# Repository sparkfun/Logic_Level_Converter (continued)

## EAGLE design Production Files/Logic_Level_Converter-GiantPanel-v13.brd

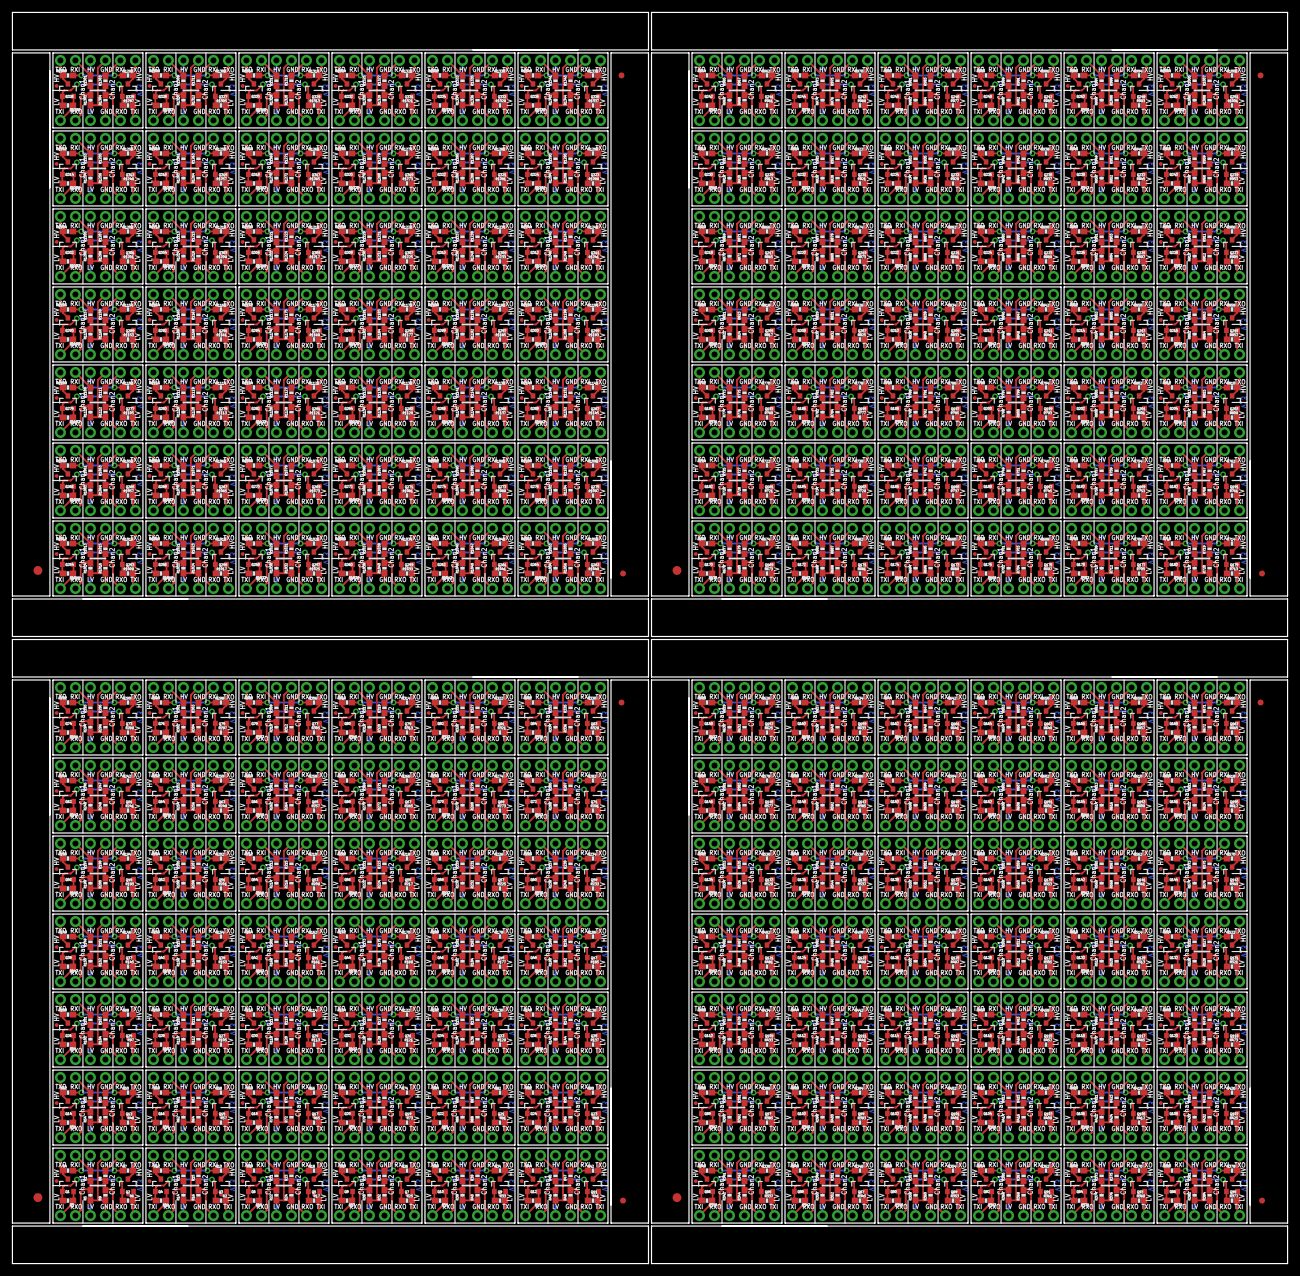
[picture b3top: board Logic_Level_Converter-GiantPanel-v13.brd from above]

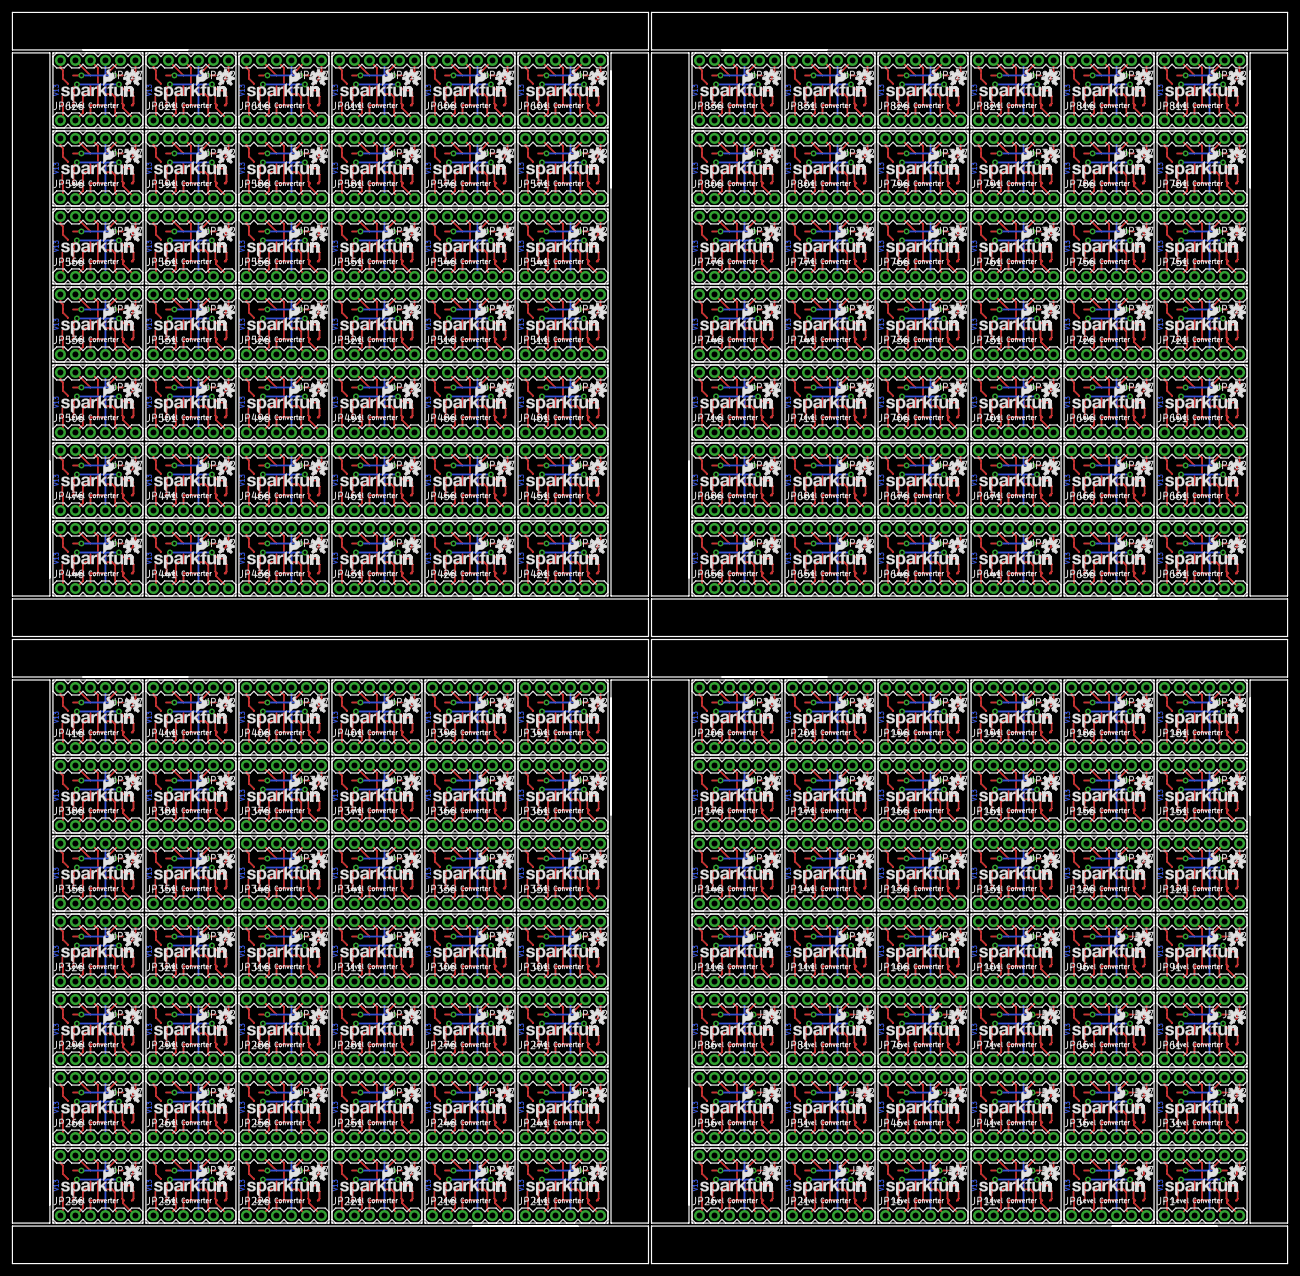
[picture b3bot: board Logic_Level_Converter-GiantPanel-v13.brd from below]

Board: 2 copper layers, 215.9 x 211.8 mm, 2868 parts (840 on the bottom side), 1848 nets.

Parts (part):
E$1, E$6, E$9, E$12: FIDUCIAL-1.5X3
E$2, E$3, E$4, E$5, E$7, E$8, E$10, E$11: FIDUCIAL-1X2
JP1, JP2, JP6, JP7, JP11, JP12, JP16, JP17, JP21, JP22, JP26, JP27, JP31, JP32, JP36, JP37, JP41, JP42, JP46, JP47, JP51, JP52, JP56, JP57, JP61, JP62, JP66, JP67, JP71, JP72, JP76, JP77, JP81, JP82, JP86, JP87, JP91, JP92, JP96, JP97, JP101, JP102, JP106, JP107, JP111, JP112, JP116, JP117, JP121, JP122, JP126, JP127, JP131, JP132, JP136, JP137, JP141, JP142, JP146, JP147, JP151, JP152, JP156, JP157, JP161, JP162, JP166, JP167, JP171, JP172, JP176, JP177, JP181, JP182, JP186, JP187, JP191, JP192, JP196, JP197, JP201, JP202, JP206, JP207, JP211, JP212, JP216, JP217, JP221, JP222, JP226, JP227, JP231, JP232, JP236, JP237, JP241, JP242, JP246, JP247, JP251, JP252, JP256, JP257, JP261, JP262, JP266, JP267, JP271, JP272, JP276, JP277, JP281, JP282, JP286, JP287, JP291, JP292, JP296, JP297, JP301, JP302, JP306, JP307, JP311, JP312, JP316, JP317, JP321, JP322, JP326, JP327, JP331, JP332, JP336, JP337, JP341, JP342, JP346, JP347, JP351, JP352, JP356, JP357, JP361, JP362, JP366, JP367, JP371, JP372, JP376, JP377, JP381, JP382, JP386, JP387, JP391, JP392, JP396, JP397, JP401, JP402, JP406, JP407, JP411, JP412, JP416, JP417, JP421, JP422, JP426, JP427, JP431, JP432, JP436, JP437, JP441, JP442, JP446, JP447, JP451, JP452, JP456, JP457, JP461, JP462, JP466, JP467, JP471, JP472, JP476, JP477, JP481, JP482, JP486, JP487, JP491, JP492, JP496, JP497, JP501, JP502, JP506, JP507, JP511, JP512, JP516, JP517, JP521, JP522, JP526, JP527, JP531, JP532, JP536, JP537, JP541, JP542, JP546, JP547, JP551, JP552, JP556, JP557, JP561, JP562, JP566, JP567, JP571, JP572, JP576, JP577, JP581, JP582, JP586, JP587, JP591, JP592, JP596, JP597, JP601, JP602, JP606, JP607, JP611, JP612, JP616, JP617, JP621, JP622, JP626, JP627, JP631, JP632, JP636, JP637, JP641, JP642, JP646, JP647, JP651, JP652, JP656, JP657, JP661, JP662, JP666, JP667, JP671, JP672, JP676, JP677, JP681, JP682, JP686, JP687, JP691, JP692, JP696, JP697, JP701, JP702, JP706, JP707, JP711, JP712, JP716, JP717, JP721, JP722, JP726, JP727, JP731, JP732, JP736, JP737, JP741, JP742, JP746, JP747, JP751, JP752, JP756, JP757, JP761, JP762, JP766, JP767, JP771, JP772, JP776, JP777, JP781, JP782, JP786, JP787, JP791, JP792, JP796, JP797, JP801, JP802, JP806, JP807, JP811, JP812, JP816, JP817, JP821, JP822, JP826, JP827, JP831, JP832, JP836, JP837: 1X06
JP3, JP4, JP8, JP9, JP13, JP14, JP18, JP19, JP23, JP24, JP28, JP29, JP33, JP34, JP38, JP39, JP43, JP44, JP48, JP49, JP53, JP54, JP58, JP59, JP63, JP64, JP68, JP69, JP73, JP74, JP78, JP79, JP83, JP84, JP88, JP89, JP93, JP94, JP98, JP99, JP103, JP104, JP108, JP109, JP113, JP114, JP118, JP119, JP123, JP124, JP128, JP129, JP133, JP134, JP138, JP139, JP143, JP144, JP148, JP149, JP153, JP154, JP158, JP159, JP163, JP164, JP168, JP169, JP173, JP174, JP178, JP179, JP183, JP184, JP188, JP189, JP193, JP194, JP198, JP199, JP203, JP204, JP208, JP209, JP213, JP214, JP218, JP219, JP223, JP224, JP228, JP229, JP233, JP234, JP238, JP239, JP243, JP244, JP248, JP249, JP253, JP254, JP258, JP259, JP263, JP264, JP268, JP269, JP273, JP274, JP278, JP279, JP283, JP284, JP288, JP289, JP293, JP294, JP298, JP299, JP303, JP304, JP308, JP309, JP313, JP314, JP318, JP319, JP323, JP324, JP328, JP329, JP333, JP334, JP338, JP339, JP343, JP344, JP348, JP349, JP353, JP354, JP358, JP359, JP363, JP364, JP368, JP369, JP373, JP374, JP378, JP379, JP383, JP384, JP388, JP389, JP393, JP394, JP398, JP399, JP403, JP404, JP408, JP409, JP413, JP414, JP418, JP419, JP423, JP424, JP428, JP429, JP433, JP434, JP438, JP439, JP443, JP444, JP448, JP449, JP453, JP454, JP458, JP459, JP463, JP464, JP468, JP469, JP473, JP474, JP478, JP479, JP483, JP484, JP488, JP489, JP493, JP494, JP498, JP499, JP503, JP504, JP508, JP509, JP513, JP514, JP518, JP519, JP523, JP524, JP528, JP529, JP533, JP534, JP538, JP539, JP543, JP544, JP548, JP549, JP553, JP554, JP558, JP559, JP563, JP564, JP568, JP569, JP573, JP574, JP578, JP579, JP583, JP584, JP588, JP589, JP593, JP594, JP598, JP599, JP603, JP604, JP608, JP609, JP613, JP614, JP618, JP619, JP623, JP624, JP628, JP629, JP633, JP634, JP638, JP639, JP643, JP644, JP648, JP649, JP653, JP654, JP658, JP659, JP663, JP664, JP668, JP669, JP673, JP674, JP678, JP679, JP683, JP684, JP688, JP689, JP693, JP694, JP698, JP699, JP703, JP704, JP708, JP709, JP713, JP714, JP718, JP719, JP723, JP724, JP728, JP729, JP733, JP734, JP738, JP739, JP743, JP744, JP748, JP749, JP753, JP754, JP758, JP759, JP763, JP764, JP768, JP769, JP773, JP774, JP778, JP779, JP783, JP784, JP788, JP789, JP793, JP794, JP798, JP799, JP803, JP804, JP808, JP809, JP813, JP814, JP818, JP819, JP823, JP824, JP828, JP829, JP833, JP834, JP838, JP839: FIDUCIALUFIDUCIAL; MICRO-FIDUCIAL
JP5, JP10, JP15, JP20, JP25, JP30, JP35, JP40, JP45, JP50, JP55, JP60, JP65, JP70, JP75, JP80, JP85, JP90, JP95, JP100, JP105, JP110, JP115, JP120, JP125, JP130, JP135, JP140, JP145, JP150, JP155, JP160, JP165, JP170, JP175, JP180, JP185, JP190, JP195, JP200, JP205, JP210, JP215, JP220, JP225, JP230, JP235, JP240, JP245, JP250, JP255, JP260, JP265, JP270, JP275, JP280, JP285, JP290, JP295, JP300, JP305, JP310, JP315, JP320, JP325, JP330, JP335, JP340, JP345, JP350, JP355, JP360, JP365, JP370, JP375, JP380, JP385, JP390, JP395, JP400, JP405, JP410, JP415, JP420, JP425, JP430, JP435, JP440, JP445, JP450, JP455, JP460, JP465, JP470, JP475, JP480, JP485, JP490, JP495, JP500, JP505, JP510, JP515, JP520, JP525, JP530, JP535, JP540, JP545, JP550, JP555, JP560, JP565, JP570, JP575, JP580, JP585, JP590, JP595, JP600, JP605, JP610, JP615, JP620, JP625, JP630, JP635, JP640, JP645, JP650, JP655, JP660, JP665, JP670, JP675, JP680, JP685, JP690, JP695, JP700, JP705, JP710, JP715, JP720, JP725, JP730, JP735, JP740, JP745, JP750, JP755, JP760, JP765, JP770, JP775, JP780, JP785, JP790, JP795, JP800, JP805, JP810, JP815, JP820, JP825, JP830, JP835, JP840: LOGO-SFENW2; SFE-NEW-WEB
Q1, Q2, Q3, Q4, Q5, Q6, Q7, Q8, Q9, Q10, Q11, Q12, Q13, Q14, Q15, Q16, Q17, Q18, Q19, Q20, Q21, Q22, Q23, Q24, Q25, Q26, Q27, Q28, Q29, Q30, Q31, Q32, Q33, Q34, Q35, Q36, Q37, Q38, Q39, Q40, Q41, Q42, Q43, Q44, Q45, Q46, Q47, Q48, Q49, Q50, Q51, Q52, Q53, Q54, Q55, Q56, Q57, Q58, Q59, Q60, Q61, Q62, Q63, Q64, Q65, Q66, Q67, Q68, Q69, Q70, Q71, Q72, Q73, Q74, Q75, Q76, Q77, Q78, Q79, Q80, Q81, Q82, Q83, Q84, Q85, Q86, Q87, Q88, Q89, Q90, Q91, Q92, Q93, Q94, Q95, Q96, Q97, Q98, Q99, Q100, Q101, Q102, Q103, Q104, Q105, Q106, Q107, Q108, Q109, Q110, Q111, Q112, Q113, Q114, Q115, Q116, Q117, Q118, Q119, Q120, Q121, Q122, Q123, Q124, Q125, Q126, Q127, Q128, Q129, Q130, Q131, Q132, Q133, Q134, Q135, Q136, Q137, Q138, Q139, Q140, Q141, Q142, Q143, Q144, Q145, Q146, Q147, Q148, Q149, Q150, Q151, Q152, Q153, Q154, Q155, Q156, Q157, Q158, Q159, Q160, Q161, Q162, Q163, Q164, Q165, Q166, Q167, Q168, Q169, Q170, Q171, Q172, Q173, Q174, Q175, Q176, Q177, Q178, Q179, Q180, Q181, Q182, Q183, Q184, Q185, Q186, Q187, Q188, Q189, Q190, Q191, Q192, Q193, Q194, Q195, Q196, Q197, Q198, Q199, Q200, Q201, Q202, Q203, Q204, Q205, Q206, Q207, Q208, Q209, Q210, Q211, Q212, Q213, Q214, Q215, Q216, Q217, Q218, Q219, Q220, Q221, Q222, Q223, Q224, Q225, Q226, Q227, Q228, Q229, Q230, Q231, Q232, Q233, Q234, Q235, Q236, Q237, Q238, Q239, Q240, Q241, Q242, Q243, Q244, Q245, Q246, Q247, Q248, Q249, Q250, Q251, Q252, Q253, Q254, Q255, Q256, Q257, Q258, Q259, Q260, Q261, Q262, Q263, Q264, Q265, Q266, Q267, Q268, Q269, Q270, Q271, Q272, Q273, Q274, Q275, Q276, Q277, Q278, Q279, Q280, Q281, Q282, Q283, Q284, Q285, Q286, Q287, Q288, Q289, Q290, Q291, Q292, Q293, Q294, Q295, Q296, Q297, Q298, Q299, Q300, Q301, Q302, Q303, Q304, Q305, Q306, Q307, Q308, Q309, Q310, Q311, Q312, Q313, Q314, Q315, Q316, Q317, Q318, Q319, Q320, Q321, Q322, Q323, Q324, Q325, Q326, Q327, Q328, Q329, Q330, Q331, Q332, Q333, Q334, Q335, Q336: BSS138; SOT23-3
R1, R2, R3, R4, R6, R7, R8, R10, R11, R12, R13, R15, R17, R18, R19, R20, R21, R23, R25, R26, R27, R28, R29, R31, R33, R34, R35, R36, R37, R39, R41, R42, R43, R44, R45, R47, R49, R50, R51, R52, R53, R55, R57, R58, R59, R60, R61, R63, R65, R66, R67, R68, R69, R71, R73, R74, R75, R76, R77, R79, R81, R82, R83, R84, R85, R87, R89, R90, R91, R92, R93, R95, R97, R98, R99, R100, R101, R103, R105, R106, R107, R108, R109, R111, R113, R114, R115, R116, R117, R119, R121, R122, R123, R124, R125, R127, R129, R130, R131, R132, R133, R135, R137, R138, R139, R140, R141, R143, R145, R146, R147, R148, R149, R151, R153, R154, R155, R156, R157, R159, R161, R162, R163, R164, R165, R167, R169, R170, R171, R172, R173, R175, R177, R178, R179, R180, R181, R183, R185, R186, R187, R188, R189, R191, R193, R194, R195, R196, R197, R199, R201, R202, R203, R204, R205, R207, R209, R210, R211, R212, R213, R215, R217, R218, R219, R220, R221, R223, R225, R226, R227, R228, R229, R231, R233, R234, R235, R236, R237, R239, R241, R242, R243, R244, R245, R247, R249, R250, R251, R252, R253, R255, R257, R258, R259, R260, R261, R263, R265, R266, R267, R268, R269, R271, R273, R274, R275, R276, R277, R279, R281, R282, R283, R284, R285, R287, R289, R290, R291, R292, R293, R295, R297, R298, R299, R300, R301, R303, R305, R306, R307, R308, R309, R311, R313, R314, R315, R316, R317, R319, R321, R322, R323, R324, R325, R327, R329, R330, R331, R332, R333, R335, R337, R338, R339, R340, R341, R343, R345, R346, R347, R348, R349, R351, R353, R354, R355, R356, R357, R359, R361, R362, R363, R364, R365, R367, R369, R370, R371, R372, R373, R375, R377, R378, R379, R380, R381, R383, R385, R386, R387, R388, R389, R391, R393, R394, R395, R396, R397, R399, R401, R402, R403, R404, R405, R407, R409, R410, R411, R412, R413, R415, R417, R418, R419, R420, R421, R423, R425, R426, R427, R428, R429, R431, R433, R434, R435, R436, R437, R439, R441, R442, R443, R444, R445, R447, R449, R450, R451, R452, R453, R455, R457, R458, R459, R460, R461, R463, R465, R466, R467, R468, R469, R471, R473, R474, R475, R476, R477, R479, R481, R482, R483, R484, R485, R487, R489, R490, R491, R492, R493, R495, R497, R498, R499, R500, R501, R503, R505, R506, R507, R508, R509, R511, R513, R514, R515, R516, R517, R519, R521, R522, R523, R524, R525, R527, R529, R530, R531, R532, R533, R535, R537, R538, R539, R540, R541, R543, R545, R546, R547, R548, R549, R551, R553, R554, R555, R556, R557, R559, R561, R562, R563, R564, R565, R567, R569, R570, R571, R572, R573, R575, R577, R578, R579, R580, R581, R583, R585, R586, R587, R588, R589, R591, R593, R594, R595, R596, R597, R599, R601, R602, R603, R604, R605, R607, R609, R610, R611, R612, R613, R615, R617, R618, R619, R620, R621, R623, R625, R626, R627, R628, R629, R631, R633, R634, R635, R636, R637, R639, R641, R642, R643, R644, R645, R647, R649, R650, R651, R652, R653, R655, R657, R658, R659, R660, R661, R663, R665, R666, R667, R668, R669, R671, R673, R674, R675, R676, R677, R679, R681, R682, R683, R684, R685, R687, R689, R690, R691, R692, R693, R695, R697, R698, R699, R700, R701, R703, R705, R706, R707, R708, R709, R711, R713, R714, R715, R716, R717, R719, R721, R722, R723, R724, R725, R727, R729, R730, R731, R732, R733, R735, R737, R738, R739, R740, R741, R743, R745, R746, R747, R748, R749, R751, R753, R754, R755, R756, R757, R759, R761, R762, R763, R764, R765, R767, R769, R770, R771, R772, R773, R775, R777, R778, R779, R780, R781, R783, R785, R786, R787, R788, R789, R791, R793, R794, R795, R796, R797, R799, R801, R802, R803, R804, R805, R807, R809, R810, R811, R812, R813, R815, R817, R818, R819, R820, R821, R823, R825, R826, R827, R828, R829, R831, R833, R834, R835, R836, R837, R839, R841, R842, R843, R844, R845, R847, R849, R850, R851, R852, R853, R855, R857, R858, R859, R860, R861, R863, R865, R866, R867, R868, R869, R871, R873, R874, R875, R876, R877, R879, R881, R882, R883, R884, R885, R887, R889, R890, R891, R892, R893, R895, R897, R898, R899, R900, R901, R903, R905, R906, R907, R908, R909, R911, R913, R914, R915, R916, R917, R919, R921, R922, R923, R924, R925, R927, R929, R930, R931, R932, R933, R935, R937, R938, R939, R940, R941, R943, R945, R946, R947, R948, R949, R951, R953, R954, R955, R956, R957, R959, R961, R962, R963, R964, R965, R967, R969, R970, R971, R972, R973, R975, R977, R978, R979, R980, R981, R983, R985, R986, R987, R988, R989, R991, R993, R994, R995, R996, R997, R999, R1001, R1002, R1003, R1004, R1005, R1007, R1009, R1010, R1011, R1012, R1013, R1015, R1017, R1018, R1019, R1020, R1021, R1023, R1025, R1026, R1027, R1028, R1029, R1031, R1033, R1034, R1035, R1036, R1037, R1039, R1041, R1042, R1043, R1044, R1045, R1047, R1049, R1050, R1051, R1052, R1053, R1055, R1057, R1058, R1059, R1060, R1061, R1063, R1065, R1066, R1067, R1068, R1069, R1071, R1073, R1074, R1075, R1076, R1077, R1079, R1081, R1082, R1083, R1084, R1085, R1087, R1089, R1090, R1091, R1092, R1093, R1095, R1097, R1098, R1099, R1100, R1101, R1103, R1105, R1106, R1107, R1108, R1109, R1111, R1113, R1114, R1115, R1116, R1117, R1119, R1121, R1122, R1123, R1124, R1125, R1127, R1129, R1130, R1131, R1132, R1133, R1135, R1137, R1138, R1139, R1140, R1141, R1143, R1145, R1146, R1147, R1148, R1149, R1151, R1153, R1154, R1155, R1156, R1157, R1159, R1161, R1162, R1163, R1164, R1165, R1167, R1169, R1170, R1171, R1172, R1173, R1175, R1177, R1178, R1179, R1180, R1181, R1183, R1185, R1186, R1187, R1188, R1189, R1191, R1193, R1194, R1195, R1196, R1197, R1199, R1201, R1202, R1203, R1204, R1205, R1207, R1209, R1210, R1211, R1212, R1213, R1215, R1217, R1218, R1219, R1220, R1221, R1223, R1225, R1226, R1227, R1228, R1229, R1231, R1233, R1234, R1235, R1236, R1237, R1239, R1241, R1242, R1243, R1244, R1245, R1247, R1249, R1250, R1251, R1252, R1253, R1255, R1257, R1258, R1259, R1260, R1261, R1263, R1265, R1266, R1267, R1268, R1269, R1271, R1273, R1274, R1275, R1276, R1277, R1279, R1281, R1282, R1283, R1284, R1285, R1287, R1289, R1290, R1291, R1292, R1293, R1295, R1297, R1298, R1299, R1300, R1301, R1303, R1305, R1306, R1307, R1308, R1309, R1311, R1313, R1314, R1315, R1316, R1317, R1319, R1321, R1322, R1323, R1324, R1325, R1327, R1329, R1330, R1331, R1332, R1333, R1335, R1337, R1338, R1339, R1340, R1341, R1343: 10K; 0603-RES
R5, R9, R14, R16, R22, R24, R30, R32, R38, R40, R46, R48, R54, R56, R62, R64, R70, R72, R78, R80, R86, R88, R94, R96, R102, R104, R110, R112, R118, R120, R126, R128, R134, R136, R142, R144, R150, R152, R158, R160, R166, R168, R174, R176, R182, R184, R190, R192, R198, R200, R206, R208, R214, R216, R222, R224, R230, R232, R238, R240, R246, R248, R254, R256, R262, R264, R270, R272, R278, R280, R286, R288, R294, R296, R302, R304, R310, R312, R318, R320, R326, R328, R334, R336, R342, R344, R350, R352, R358, R360, R366, R368, R374, R376, R382, R384, R390, R392, R398, R400, R406, R408, R414, R416, R422, R424, R430, R432, R438, R440, R446, R448, R454, R456, R462, R464, R470, R472, R478, R480, R486, R488, R494, R496, R502, R504, R510, R512, R518, R520, R526, R528, R534, R536, R542, R544, R550, R552, R558, R560, R566, R568, R574, R576, R582, R584, R590, R592, R598, R600, R606, R608, R614, R616, R622, R624, R630, R632, R638, R640, R646, R648, R654, R656, R662, R664, R670, R672, R678, R680, R686, R688, R694, R696, R702, R704, R710, R712, R718, R720, R726, R728, R734, R736, R742, R744, R750, R752, R758, R760, R766, R768, R774, R776, R782, R784, R790, R792, R798, R800, R806, R808, R814, R816, R822, R824, R830, R832, R838, R840, R846, R848, R854, R856, R862, R864, R870, R872, R878, R880, R886, R888, R894, R896, R902, R904, R910, R912, R918, R920, R926, R928, R934, R936, R942, R944, R950, R952, R958, R960, R966, R968, R974, R976, R982, R984, R990, R992, R998, R1000, R1006, R1008, R1014, R1016, R1022, R1024, R1030, R1032, R1038, R1040, R1046, R1048, R1054, R1056, R1062, R1064, R1070, R1072, R1078, R1080, R1086, R1088, R1094, R1096, R1102, R1104, R1110, R1112, R1118, R1120, R1126, R1128, R1134, R1136, R1142, R1144, R1150, R1152, R1158, R1160, R1166, R1168, R1174, R1176, R1182, R1184, R1190, R1192, R1198, R1200, R1206, R1208, R1214, R1216, R1222, R1224, R1230, R1232, R1238, R1240, R1246, R1248, R1254, R1256, R1262, R1264, R1270, R1272, R1278, R1280, R1286, R1288, R1294, R1296, R1302, R1304, R1310, R1312, R1318, R1320, R1326, R1328, R1334, R1336, R1342, R1344: 20K; 0603-RES
U$1, U$3, U$5, U$7, U$9, U$11, U$13, U$15, U$17, U$19, U$21, U$23, U$25, U$27, U$29, U$31, U$33, U$35, U$37, U$39, U$41, U$43, U$45, U$47, U$49, U$51, U$53, U$55, U$57, U$59, U$61, U$63, U$65, U$67, U$69, U$71, U$73, U$75, U$77, U$79, U$81, U$83, U$85, U$87, U$89, U$91, U$93, U$95, U$97, U$99, U$101, U$103, U$105, U$107, U$109, U$111, U$113, U$115, U$117, U$119, U$121, U$123, U$125, U$127, U$129, U$131, U$133, U$135, U$137, U$139, U$141, U$143, U$145, U$147, U$149, U$151, U$153, U$155, U$157, U$159, U$161, U$163, U$165, U$167, U$169, U$171, U$173, U$175, U$177, U$179, U$181, U$183, U$185, U$187, U$189, U$191, U$193, U$195, U$197, U$199, U$201, U$203, U$205, U$207, U$209, U$211, U$213, U$215, U$217, U$219, U$221, U$223, U$225, U$227, U$229, U$231, U$233, U$235, U$237, U$239, U$241, U$243, U$245, U$247, U$249, U$251, U$253, U$255, U$257, U$259, U$261, U$263, U$265, U$267, U$269, U$271, U$273, U$275, U$277, U$279, U$281, U$283, U$285, U$287, U$289, U$291, U$293, U$295, U$297, U$299, U$301, U$303, U$305, U$307, U$309, U$311, U$313, U$315, U$317, U$319, U$321, U$323, U$325, U$327, U$329, U$331, U$333, U$335: LOGO-SFESK; SFE-LOGO-FLAME
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
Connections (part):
GND: JP1.3, JP2.4, R5.1, R9.1
GND1: JP6.3, JP7.4, R14.1, R16.1
GND2: JP11.3, JP12.4, R22.1, R24.1
GND3: JP16.3, JP17.4, R30.1, R32.1
GND4: JP21.3, JP22.4, R38.1, R40.1
GND5: JP26.3, JP27.4, R46.1, R48.1
GND6: JP31.3, JP32.4, R54.1, R56.1
GND7: JP36.3, JP37.4, R62.1, R64.1
GND8: JP41.3, JP42.4, R70.1, R72.1
GND9: JP46.3, JP47.4, R78.1, R80.1
GND10: JP51.3, JP52.4, R86.1, R88.1
GND11: JP56.3, JP57.4, R94.1, R96.1
GND12: JP61.3, JP62.4, R102.1, R104.1
GND13: JP66.3, JP67.4, R110.1, R112.1
GND14: JP71.3, JP72.4, R118.1, R120.1
GND15: JP76.3, JP77.4, R126.1, R128.1
GND16: JP81.3, JP82.4, R134.1, R136.1
GND17: JP86.3, JP87.4, R142.1, R144.1
GND18: JP91.3, JP92.4, R150.1, R152.1
GND19: JP96.3, JP97.4, R158.1, R160.1
GND20: JP101.3, JP102.4, R166.1, R168.1
GND21: JP106.3, JP107.4, R174.1, R176.1
GND22: JP111.3, JP112.4, R182.1, R184.1
GND23: JP116.3, JP117.4, R190.1, R192.1
GND24: JP121.3, JP122.4, R198.1, R200.1
GND25: JP126.3, JP127.4, R206.1, R208.1
GND26: JP131.3, JP132.4, R214.1, R216.1
GND27: JP136.3, JP137.4, R222.1, R224.1
GND28: JP141.3, JP142.4, R230.1, R232.1
GND29: JP146.3, JP147.4, R238.1, R240.1
GND30: JP151.3, JP152.4, R246.1, R248.1
GND31: JP156.3, JP157.4, R254.1, R256.1
GND32: JP161.3, JP162.4, R262.1, R264.1
GND33: JP166.3, JP167.4, R270.1, R272.1
GND34: JP171.3, JP172.4, R278.1, R280.1
GND35: JP176.3, JP177.4, R286.1, R288.1
GND36: JP181.3, JP182.4, R294.1, R296.1
GND37: JP186.3, JP187.4, R302.1, R304.1
GND38: JP191.3, JP192.4, R310.1, R312.1
GND39: JP196.3, JP197.4, R318.1, R320.1
GND40: JP201.3, JP202.4, R326.1, R328.1
GND41: JP206.3, JP207.4, R334.1, R336.1
GND42: JP211.3, JP212.4, R342.1, R344.1
GND43: JP216.3, JP217.4, R350.1, R352.1
GND44: JP221.3, JP222.4, R358.1, R360.1
GND45: JP226.3, JP227.4, R366.1, R368.1
GND46: JP231.3, JP232.4, R374.1, R376.1
GND47: JP236.3, JP237.4, R382.1, R384.1
GND48: JP241.3, JP242.4, R390.1, R392.1
GND49: JP246.3, JP247.4, R398.1, R400.1
GND50: JP251.3, JP252.4, R406.1, R408.1
GND51: JP256.3, JP257.4, R414.1, R416.1
GND52: JP261.3, JP262.4, R422.1, R424.1
GND53: JP266.3, JP267.4, R430.1, R432.1
GND54: JP271.3, JP272.4, R438.1, R440.1
GND55: JP276.3, JP277.4, R446.1, R448.1
GND56: JP281.3, JP282.4, R454.1, R456.1
GND57: JP286.3, JP287.4, R462.1, R464.1
GND58: JP291.3, JP292.4, R470.1, R472.1
GND59: JP296.3, JP297.4, R478.1, R480.1
GND60: JP301.3, JP302.4, R486.1, R488.1
GND61: JP306.3, JP307.4, R494.1, R496.1
GND62: JP311.3, JP312.4, R502.1, R504.1
GND63: JP316.3, JP317.4, R510.1, R512.1
GND64: JP321.3, JP322.4, R518.1, R520.1
GND65: JP326.3, JP327.4, R526.1, R528.1
GND66: JP331.3, JP332.4, R534.1, R536.1
GND67: JP336.3, JP337.4, R542.1, R544.1
GND68: JP341.3, JP342.4, R550.1, R552.1
GND69: JP346.3, JP347.4, R558.1, R560.1
GND70: JP351.3, JP352.4, R566.1, R568.1
GND71: JP356.3, JP357.4, R574.1, R576.1
GND72: JP361.3, JP362.4, R582.1, R584.1
GND73: JP366.3, JP367.4, R590.1, R592.1
GND74: JP371.3, JP372.4, R598.1, R600.1
GND75: JP376.3, JP377.4, R606.1, R608.1
GND76: JP381.3, JP382.4, R614.1, R616.1
GND77: JP386.3, JP387.4, R622.1, R624.1
GND78: JP391.3, JP392.4, R630.1, R632.1
GND79: JP396.3, JP397.4, R638.1, R640.1
GND80: JP401.3, JP402.4, R646.1, R648.1
GND81: JP406.3, JP407.4, R654.1, R656.1
GND82: JP411.3, JP412.4, R662.1, R664.1
GND83: JP416.3, JP417.4, R670.1, R672.1
GND84: JP421.3, JP422.4, R678.1, R680.1
GND85: JP426.3, JP427.4, R686.1, R688.1
GND86: JP431.3, JP432.4, R694.1, R696.1
GND87: JP436.3, JP437.4, R702.1, R704.1
GND88: JP441.3, JP442.4, R710.1, R712.1
GND89: JP446.3, JP447.4, R718.1, R720.1
GND90: JP451.3, JP452.4, R726.1, R728.1
GND91: JP456.3, JP457.4, R734.1, R736.1
GND92: JP461.3, JP462.4, R742.1, R744.1
GND93: JP466.3, JP467.4, R750.1, R752.1
GND94: JP471.3, JP472.4, R758.1, R760.1
GND95: JP476.3, JP477.4, R766.1, R768.1
GND96: JP481.3, JP482.4, R774.1, R776.1
GND97: JP486.3, JP487.4, R782.1, R784.1
GND98: JP491.3, JP492.4, R790.1, R792.1
GND99: JP496.3, JP497.4, R798.1, R800.1
GND100: JP501.3, JP502.4, R806.1, R808.1
GND101: JP506.3, JP507.4, R814.1, R816.1
GND102: JP511.3, JP512.4, R822.1, R824.1
GND103: JP516.3, JP517.4, R830.1, R832.1
GND104: JP521.3, JP522.4, R838.1, R840.1
GND105: JP526.3, JP527.4, R846.1, R848.1
GND106: JP531.3, JP532.4, R854.1, R856.1
GND107: JP536.3, JP537.4, R862.1, R864.1
GND108: JP541.3, JP542.4, R870.1, R872.1
GND109: JP546.3, JP547.4, R878.1, R880.1
GND110: JP551.3, JP552.4, R886.1, R888.1
GND111: JP556.3, JP557.4, R894.1, R896.1
GND112: JP561.3, JP562.4, R902.1, R904.1
GND113: JP566.3, JP567.4, R910.1, R912.1
GND114: JP571.3, JP572.4, R918.1, R920.1
GND115: JP576.3, JP577.4, R926.1, R928.1
GND116: JP581.3, JP582.4, R934.1, R936.1
GND117: JP586.3, JP587.4, R942.1, R944.1
GND118: JP591.3, JP592.4, R950.1, R952.1
GND119: JP596.3, JP597.4, R958.1, R960.1
GND120: JP601.3, JP602.4, R966.1, R968.1
GND121: JP606.3, JP607.4, R974.1, R976.1
GND122: JP611.3, JP612.4, R982.1, R984.1
GND123: JP616.3, JP617.4, R990.1, R992.1
GND124: JP621.3, JP622.4, R998.1, R1000.1
GND125: JP626.3, JP627.4, R1006.1, R1008.1
GND126: JP631.3, JP632.4, R1014.1, R1016.1
GND127: JP636.3, JP637.4, R1022.1, R1024.1
GND128: JP641.3, JP642.4, R1030.1, R1032.1
GND129: JP646.3, JP647.4, R1038.1, R1040.1
GND130: JP651.3, JP652.4, R1046.1, R1048.1
GND131: JP656.3, JP657.4, R1054.1, R1056.1
GND132: JP661.3, JP662.4, R1062.1, R1064.1
GND133: JP666.3, JP667.4, R1070.1, R1072.1
GND134: JP671.3, JP672.4, R1078.1, R1080.1
GND135: JP676.3, JP677.4, R1086.1, R1088.1
GND136: JP681.3, JP682.4, R1094.1, R1096.1
GND137: JP686.3, JP687.4, R1102.1, R1104.1
GND138: JP691.3, JP692.4, R1110.1, R1112.1
GND139: JP696.3, JP697.4, R1118.1, R1120.1
GND140: JP701.3, JP702.4, R1126.1, R1128.1
GND141: JP706.3, JP707.4, R1134.1, R1136.1
GND142: JP711.3, JP712.4, R1142.1, R1144.1
GND143: JP716.3, JP717.4, R1150.1, R1152.1
GND144: JP721.3, JP722.4, R1158.1, R1160.1
GND145: JP726.3, JP727.4, R1166.1, R1168.1
GND146: JP731.3, JP732.4, R1174.1, R1176.1
GND147: JP736.3, JP737.4, R1182.1, R1184.1
GND148: JP741.3, JP742.4, R1190.1, R1192.1
GND149: JP746.3, JP747.4, R1198.1, R1200.1
GND150: JP751.3, JP752.4, R1206.1, R1208.1
GND151: JP756.3, JP757.4, R1214.1, R1216.1
GND152: JP761.3, JP762.4, R1222.1, R1224.1
GND153: JP766.3, JP767.4, R1230.1, R1232.1
GND154: JP771.3, JP772.4, R1238.1, R1240.1
GND155: JP776.3, JP777.4, R1246.1, R1248.1
GND156: JP781.3, JP782.4, R1254.1, R1256.1
GND157: JP786.3, JP787.4, R1262.1, R1264.1
GND158: JP791.3, JP792.4, R1270.1, R1272.1
GND159: JP796.3, JP797.4, R1278.1, R1280.1
GND160: JP801.3, JP802.4, R1286.1, R1288.1
GND161: JP806.3, JP807.4, R1294.1, R1296.1
GND162: JP811.3, JP812.4, R1302.1, R1304.1
GND163: JP816.3, JP817.4, R1310.1, R1312.1
GND164: JP821.3, JP822.4, R1318.1, R1320.1
GND165: JP826.3, JP827.4, R1326.1, R1328.1
GND166: JP831.3, JP832.4, R1334.1, R1336.1
GND167: JP836.3, JP837.4, R1342.1, R1344.1
HV: JP2.3, R4.1, R7.1
HV1: JP7.3, R10.1, R12.1
HV2: JP12.3, R18.1, R20.1
HV3: JP17.3, R26.1, R28.1
HV4: JP22.3, R34.1, R36.1
HV5: JP27.3, R42.1, R44.1
HV6: JP32.3, R50.1, R52.1
HV7: JP37.3, R58.1, R60.1
HV8: JP42.3, R66.1, R68.1
HV9: JP47.3, R74.1, R76.1
HV10: JP52.3, R82.1, R84.1
HV11: JP57.3, R90.1, R92.1
HV12: JP62.3, R98.1, R100.1
HV13: JP67.3, R106.1, R108.1
HV14: JP72.3, R114.1, R116.1
HV15: JP77.3, R122.1, R124.1
HV16: JP82.3, R130.1, R132.1
HV17: JP87.3, R138.1, R140.1
HV18: JP92.3, R146.1, R148.1
HV19: JP97.3, R154.1, R156.1
HV20: JP102.3, R162.1, R164.1
HV21: JP107.3, R170.1, R172.1
HV22: JP112.3, R178.1, R180.1
HV23: JP117.3, R186.1, R188.1
HV24: JP122.3, R194.1, R196.1
HV25: JP127.3, R202.1, R204.1
HV26: JP132.3, R210.1, R212.1
HV27: JP137.3, R218.1, R220.1
HV28: JP142.3, R226.1, R228.1
HV29: JP147.3, R234.1, R236.1
HV30: JP152.3, R242.1, R244.1
HV31: JP157.3, R250.1, R252.1
HV32: JP162.3, R258.1, R260.1
HV33: JP167.3, R266.1, R268.1
HV34: JP172.3, R274.1, R276.1
HV35: JP177.3, R282.1, R284.1
HV36: JP182.3, R290.1, R292.1
HV37: JP187.3, R298.1, R300.1
HV38: JP192.3, R306.1, R308.1
HV39: JP197.3, R314.1, R316.1
HV40: JP202.3, R322.1, R324.1
HV41: JP207.3, R330.1, R332.1
HV42: JP212.3, R338.1, R340.1
HV43: JP217.3, R346.1, R348.1
HV44: JP222.3, R354.1, R356.1
HV45: JP227.3, R362.1, R364.1
HV46: JP232.3, R370.1, R372.1
HV47: JP237.3, R378.1, R380.1
HV48: JP242.3, R386.1, R388.1
HV49: JP247.3, R394.1, R396.1
HV50: JP252.3, R402.1, R404.1
HV51: JP257.3, R410.1, R412.1
HV52: JP262.3, R418.1, R420.1
HV53: JP267.3, R426.1, R428.1
HV54: JP272.3, R434.1, R436.1
HV55: JP277.3, R442.1, R444.1
HV56: JP282.3, R450.1, R452.1
HV57: JP287.3, R458.1, R460.1
HV58: JP292.3, R466.1, R468.1
HV59: JP297.3, R474.1, R476.1
HV60: JP302.3, R482.1, R484.1
HV61: JP307.3, R490.1, R492.1
HV62: JP312.3, R498.1, R500.1
HV63: JP317.3, R506.1, R508.1
HV64: JP322.3, R514.1, R516.1
HV65: JP327.3, R522.1, R524.1
HV66: JP332.3, R530.1, R532.1
HV67: JP337.3, R538.1, R540.1
HV68: JP342.3, R546.1, R548.1
HV69: JP347.3, R554.1, R556.1
HV70: JP352.3, R562.1, R564.1
HV71: JP357.3, R570.1, R572.1
HV72: JP362.3, R578.1, R580.1
HV73: JP367.3, R586.1, R588.1
HV74: JP372.3, R594.1, R596.1
HV75: JP377.3, R602.1, R604.1
HV76: JP382.3, R610.1, R612.1
HV77: JP387.3, R618.1, R620.1
HV78: JP392.3, R626.1, R628.1
HV79: JP397.3, R634.1, R636.1
HV80: JP402.3, R642.1, R644.1
HV81: JP407.3, R650.1, R652.1
HV82: JP412.3, R658.1, R660.1
HV83: JP417.3, R666.1, R668.1
HV84: JP422.3, R674.1, R676.1
HV85: JP427.3, R682.1, R684.1
HV86: JP432.3, R690.1, R692.1
HV87: JP437.3, R698.1, R700.1
HV88: JP442.3, R706.1, R708.1
HV89: JP447.3, R714.1, R716.1
HV90: JP452.3, R722.1, R724.1
HV91: JP457.3, R730.1, R732.1
HV92: JP462.3, R738.1, R740.1
HV93: JP467.3, R746.1, R748.1
HV94: JP472.3, R754.1, R756.1
HV95: JP477.3, R762.1, R764.1
HV96: JP482.3, R770.1, R772.1
HV97: JP487.3, R778.1, R780.1
HV98: JP492.3, R786.1, R788.1
HV99: JP497.3, R794.1, R796.1
HV100: JP502.3, R802.1, R804.1
HV101: JP507.3, R810.1, R812.1
HV102: JP512.3, R818.1, R820.1
HV103: JP517.3, R826.1, R828.1
HV104: JP522.3, R834.1, R836.1
HV105: JP527.3, R842.1, R844.1
HV106: JP532.3, R850.1, R852.1
HV107: JP537.3, R858.1, R860.1
HV108: JP542.3, R866.1, R868.1
HV109: JP547.3, R874.1, R876.1
HV110: JP552.3, R882.1, R884.1
HV111: JP557.3, R890.1, R892.1
HV112: JP562.3, R898.1, R900.1
HV113: JP567.3, R906.1, R908.1
HV114: JP572.3, R914.1, R916.1
HV115: JP577.3, R922.1, R924.1
HV116: JP582.3, R930.1, R932.1
HV117: JP587.3, R938.1, R940.1
HV118: JP592.3, R946.1, R948.1
HV119: JP597.3, R954.1, R956.1
HV120: JP602.3, R962.1, R964.1
HV121: JP607.3, R970.1, R972.1
HV122: JP612.3, R978.1, R980.1
HV123: JP617.3, R986.1, R988.1
HV124: JP622.3, R994.1, R996.1
HV125: JP627.3, R1002.1, R1004.1
HV126: JP632.3, R1010.1, R1012.1
HV127: JP637.3, R1018.1, R1020.1
HV128: JP642.3, R1026.1, R1028.1
HV129: JP647.3, R1034.1, R1036.1
HV130: JP652.3, R1042.1, R1044.1
HV131: JP657.3, R1050.1, R1052.1
HV132: JP662.3, R1058.1, R1060.1
HV133: JP667.3, R1066.1, R1068.1
HV134: JP672.3, R1074.1, R1076.1
HV135: JP677.3, R1082.1, R1084.1
HV136: JP682.3, R1090.1, R1092.1
HV137: JP687.3, R1098.1, R1100.1
HV138: JP692.3, R1106.1, R1108.1
HV139: JP697.3, R1114.1, R1116.1
HV140: JP702.3, R1122.1, R1124.1
HV141: JP707.3, R1130.1, R1132.1
HV142: JP712.3, R1138.1, R1140.1
HV143: JP717.3, R1146.1, R1148.1
HV144: JP722.3, R1154.1, R1156.1
HV145: JP727.3, R1162.1, R1164.1
HV146: JP732.3, R1170.1, R1172.1
HV147: JP737.3, R1178.1, R1180.1
HV148: JP742.3, R1186.1, R1188.1
HV149: JP747.3, R1194.1, R1196.1
HV150: JP752.3, R1202.1, R1204.1
HV151: JP757.3, R1210.1, R1212.1
HV152: JP762.3, R1218.1, R1220.1
HV153: JP767.3, R1226.1, R1228.1
HV154: JP772.3, R1234.1, R1236.1
HV155: JP777.3, R1242.1, R1244.1
HV156: JP782.3, R1250.1, R1252.1
HV157: JP787.3, R1258.1, R1260.1
HV158: JP792.3, R1266.1, R1268.1
HV159: JP797.3, R1274.1, R1276.1
HV160: JP802.3, R1282.1, R1284.1
HV161: JP807.3, R1290.1, R1292.1
HV162: JP812.3, R1298.1, R1300.1
HV163: JP817.3, R1306.1, R1308.1
HV164: JP822.3, R1314.1, R1316.1
HV165: JP827.3, R1322.1, R1324.1
HV166: JP832.3, R1330.1, R1332.1
HV167: JP837.3, R1338.1, R1340.1
LV: JP1.4, Q1.1, Q2.1, R3.1, R6.1
LV1: JP6.4, Q3.1, Q4.1, R2.1, R11.1
LV2: JP11.4, Q5.1, Q6.1, R17.1, R19.1
LV3: JP16.4, Q7.1, Q8.1, R25.1, R27.1
LV4: JP21.4, Q9.1, Q10.1, R33.1, R35.1
LV5: JP26.4, Q11.1, Q12.1, R41.1, R43.1
LV6: JP31.4, Q13.1, Q14.1, R49.1, R51.1
LV7: JP36.4, Q15.1, Q16.1, R57.1, R59.1
LV8: JP41.4, Q17.1, Q18.1, R65.1, R67.1
LV9: JP46.4, Q19.1, Q20.1, R73.1, R75.1
LV10: JP51.4, Q21.1, Q22.1, R81.1, R83.1
LV11: JP56.4, Q23.1, Q24.1, R89.1, R91.1
LV12: JP61.4, Q25.1, Q26.1, R97.1, R99.1
LV13: JP66.4, Q27.1, Q28.1, R105.1, R107.1
LV14: JP71.4, Q29.1, Q30.1, R113.1, R115.1
LV15: JP76.4, Q31.1, Q32.1, R121.1, R123.1
LV16: JP81.4, Q33.1, Q34.1, R129.1, R131.1
LV17: JP86.4, Q35.1, Q36.1, R137.1, R139.1
LV18: JP91.4, Q37.1, Q38.1, R145.1, R147.1
LV19: JP96.4, Q39.1, Q40.1, R153.1, R155.1
LV20: JP101.4, Q41.1, Q42.1, R161.1, R163.1
LV21: JP106.4, Q43.1, Q44.1, R169.1, R171.1
LV22: JP111.4, Q45.1, Q46.1, R177.1, R179.1
LV23: JP116.4, Q47.1, Q48.1, R185.1, R187.1
LV24: JP121.4, Q49.1, Q50.1, R193.1, R195.1
LV25: JP126.4, Q51.1, Q52.1, R201.1, R203.1
LV26: JP131.4, Q53.1, Q54.1, R209.1, R211.1
LV27: JP136.4, Q55.1, Q56.1, R217.1, R219.1
LV28: JP141.4, Q57.1, Q58.1, R225.1, R227.1
LV29: JP146.4, Q59.1, Q60.1, R233.1, R235.1
LV30: JP151.4, Q61.1, Q62.1, R241.1, R243.1
LV31: JP156.4, Q63.1, Q64.1, R249.1, R251.1
LV32: JP161.4, Q65.1, Q66.1, R257.1, R259.1
LV33: JP166.4, Q67.1, Q68.1, R265.1, R267.1
LV34: JP171.4, Q69.1, Q70.1, R273.1, R275.1
LV35: JP176.4, Q71.1, Q72.1, R281.1, R283.1
LV36: JP181.4, Q73.1, Q74.1, R289.1, R291.1
LV37: JP186.4, Q75.1, Q76.1, R297.1, R299.1
LV38: JP191.4, Q77.1, Q78.1, R305.1, R307.1
LV39: JP196.4, Q79.1, Q80.1, R313.1, R315.1
LV40: JP201.4, Q81.1, Q82.1, R321.1, R323.1
LV41: JP206.4, Q83.1, Q84.1, R329.1, R331.1
LV42: JP211.4, Q85.1, Q86.1, R337.1, R339.1
LV43: JP216.4, Q87.1, Q88.1, R345.1, R347.1
LV44: JP221.4, Q89.1, Q90.1, R353.1, R355.1
LV45: JP226.4, Q91.1, Q92.1, R361.1, R363.1
LV46: JP231.4, Q93.1, Q94.1, R369.1, R371.1
LV47: JP236.4, Q95.1, Q96.1, R377.1, R379.1
LV48: JP241.4, Q97.1, Q98.1, R385.1, R387.1
LV49: JP246.4, Q99.1, Q100.1, R393.1, R395.1
LV50: JP251.4, Q101.1, Q102.1, R401.1, R403.1
LV51: JP256.4, Q103.1, Q104.1, R409.1, R411.1
LV52: JP261.4, Q105.1, Q106.1, R417.1, R419.1
LV53: JP266.4, Q107.1, Q108.1, R425.1, R427.1
LV54: JP271.4, Q109.1, Q110.1, R433.1, R435.1
LV55: JP276.4, Q111.1, Q112.1, R441.1, R443.1
LV56: JP281.4, Q113.1, Q114.1, R449.1, R451.1
LV57: JP286.4, Q115.1, Q116.1, R457.1, R459.1
LV58: JP291.4, Q117.1, Q118.1, R465.1, R467.1
LV59: JP296.4, Q119.1, Q120.1, R473.1, R475.1
LV60: JP301.4, Q121.1, Q122.1, R481.1, R483.1
LV61: JP306.4, Q123.1, Q124.1, R489.1, R491.1
LV62: JP311.4, Q125.1, Q126.1, R497.1, R499.1
LV63: JP316.4, Q127.1, Q128.1, R505.1, R507.1
LV64: JP321.4, Q129.1, Q130.1, R513.1, R515.1
LV65: JP326.4, Q131.1, Q132.1, R521.1, R523.1
LV66: JP331.4, Q133.1, Q134.1, R529.1, R531.1
LV67: JP336.4, Q135.1, Q136.1, R537.1, R539.1
LV68: JP341.4, Q137.1, Q138.1, R545.1, R547.1
LV69: JP346.4, Q139.1, Q140.1, R553.1, R555.1
LV70: JP351.4, Q141.1, Q142.1, R561.1, R563.1
LV71: JP356.4, Q143.1, Q144.1, R569.1, R571.1
LV72: JP361.4, Q145.1, Q146.1, R577.1, R579.1
LV73: JP366.4, Q147.1, Q148.1, R585.1, R587.1
LV74: JP371.4, Q149.1, Q150.1, R593.1, R595.1
LV75: JP376.4, Q151.1, Q152.1, R601.1, R603.1
LV76: JP381.4, Q153.1, Q154.1, R609.1, R611.1
LV77: JP386.4, Q155.1, Q156.1, R617.1, R619.1
LV78: JP391.4, Q157.1, Q158.1, R625.1, R627.1
LV79: JP396.4, Q159.1, Q160.1, R633.1, R635.1
LV80: JP401.4, Q161.1, Q162.1, R641.1, R643.1
LV81: JP406.4, Q163.1, Q164.1, R649.1, R651.1
LV82: JP411.4, Q165.1, Q166.1, R657.1, R659.1
LV83: JP416.4, Q167.1, Q168.1, R665.1, R667.1
LV84: JP421.4, Q169.1, Q170.1, R673.1, R675.1
LV85: JP426.4, Q171.1, Q172.1, R681.1, R683.1
LV86: JP431.4, Q173.1, Q174.1, R689.1, R691.1
LV87: JP436.4, Q175.1, Q176.1, R697.1, R699.1
LV88: JP441.4, Q177.1, Q178.1, R705.1, R707.1
LV89: JP446.4, Q179.1, Q180.1, R713.1, R715.1
LV90: JP451.4, Q181.1, Q182.1, R721.1, R723.1
LV91: JP456.4, Q183.1, Q184.1, R729.1, R731.1
LV92: JP461.4, Q185.1, Q186.1, R737.1, R739.1
LV93: JP466.4, Q187.1, Q188.1, R745.1, R747.1
LV94: JP471.4, Q189.1, Q190.1, R753.1, R755.1
LV95: JP476.4, Q191.1, Q192.1, R761.1, R763.1
LV96: JP481.4, Q193.1, Q194.1, R769.1, R771.1
LV97: JP486.4, Q195.1, Q196.1, R777.1, R779.1
LV98: JP491.4, Q197.1, Q198.1, R785.1, R787.1
LV99: JP496.4, Q199.1, Q200.1, R793.1, R795.1
LV100: JP501.4, Q201.1, Q202.1, R801.1, R803.1
LV101: JP506.4, Q203.1, Q204.1, R809.1, R811.1
LV102: JP511.4, Q205.1, Q206.1, R817.1, R819.1
LV103: JP516.4, Q207.1, Q208.1, R825.1, R827.1
LV104: JP521.4, Q209.1, Q210.1, R833.1, R835.1
LV105: JP526.4, Q211.1, Q212.1, R841.1, R843.1
LV106: JP531.4, Q213.1, Q214.1, R849.1, R851.1
LV107: JP536.4, Q215.1, Q216.1, R857.1, R859.1
LV108: JP541.4, Q217.1, Q218.1, R865.1, R867.1
LV109: JP546.4, Q219.1, Q220.1, R873.1, R875.1
LV110: JP551.4, Q221.1, Q222.1, R881.1, R883.1
LV111: JP556.4, Q223.1, Q224.1, R889.1, R891.1
LV112: JP561.4, Q225.1, Q226.1, R897.1, R899.1
LV113: JP566.4, Q227.1, Q228.1, R905.1, R907.1
LV114: JP571.4, Q229.1, Q230.1, R913.1, R915.1
LV115: JP576.4, Q231.1, Q232.1, R921.1, R923.1
LV116: JP581.4, Q233.1, Q234.1, R929.1, R931.1
LV117: JP586.4, Q235.1, Q236.1, R937.1, R939.1
LV118: JP591.4, Q237.1, Q238.1, R945.1, R947.1
LV119: JP596.4, Q239.1, Q240.1, R953.1, R955.1
LV120: JP601.4, Q241.1, Q242.1, R961.1, R963.1
LV121: JP606.4, Q243.1, Q244.1, R969.1, R971.1
LV122: JP611.4, Q245.1, Q246.1, R977.1, R979.1
LV123: JP616.4, Q247.1, Q248.1, R985.1, R987.1
LV124: JP621.4, Q249.1, Q250.1, R993.1, R995.1
LV125: JP626.4, Q251.1, Q252.1, R1001.1, R1003.1
LV126: JP631.4, Q253.1, Q254.1, R1009.1, R1011.1
LV127: JP636.4, Q255.1, Q256.1, R1017.1, R1019.1
LV128: JP641.4, Q257.1, Q258.1, R1025.1, R1027.1
LV129: JP646.4, Q259.1, Q260.1, R1033.1, R1035.1
LV130: JP651.4, Q261.1, Q262.1, R1041.1, R1043.1
LV131: JP656.4, Q263.1, Q264.1, R1049.1, R1051.1
LV132: JP661.4, Q265.1, Q266.1, R1057.1, R1059.1
LV133: JP666.4, Q267.1, Q268.1, R1065.1, R1067.1
LV134: JP671.4, Q269.1, Q270.1, R1073.1, R1075.1
LV135: JP676.4, Q271.1, Q272.1, R1081.1, R1083.1
LV136: JP681.4, Q273.1, Q274.1, R1089.1, R1091.1
LV137: JP686.4, Q275.1, Q276.1, R1097.1, R1099.1
LV138: JP691.4, Q277.1, Q278.1, R1105.1, R1107.1
LV139: JP696.4, Q279.1, Q280.1, R1113.1, R1115.1
LV140: JP701.4, Q281.1, Q282.1, R1121.1, R1123.1
LV141: JP706.4, Q283.1, Q284.1, R1129.1, R1131.1
LV142: JP711.4, Q285.1, Q286.1, R1137.1, R1139.1
LV143: JP716.4, Q287.1, Q288.1, R1145.1, R1147.1
LV144: JP721.4, Q289.1, Q290.1, R1153.1, R1155.1
LV145: JP726.4, Q291.1, Q292.1, R1161.1, R1163.1
LV146: JP731.4, Q293.1, Q294.1, R1169.1, R1171.1
LV147: JP736.4, Q295.1, Q296.1, R1177.1, R1179.1
LV148: JP741.4, Q297.1, Q298.1, R1185.1, R1187.1
LV149: JP746.4, Q299.1, Q300.1, R1193.1, R1195.1
LV150: JP751.4, Q301.1, Q302.1, R1201.1, R1203.1
LV151: JP756.4, Q303.1, Q304.1, R1209.1, R1211.1
LV152: JP761.4, Q305.1, Q306.1, R1217.1, R1219.1
LV153: JP766.4, Q307.1, Q308.1, R1225.1, R1227.1
LV154: JP771.4, Q309.1, Q310.1, R1233.1, R1235.1
LV155: JP776.4, Q311.1, Q312.1, R1241.1, R1243.1
LV156: JP781.4, Q313.1, Q314.1, R1249.1, R1251.1
LV157: JP786.4, Q315.1, Q316.1, R1257.1, R1259.1
LV158: JP791.4, Q317.1, Q318.1, R1265.1, R1267.1
LV159: JP796.4, Q319.1, Q320.1, R1273.1, R1275.1
LV160: JP801.4, Q321.1, Q322.1, R1281.1, R1283.1
LV161: JP806.4, Q323.1, Q324.1, R1289.1, R1291.1
LV162: JP811.4, Q325.1, Q326.1, R1297.1, R1299.1
LV163: JP816.4, Q327.1, Q328.1, R1305.1, R1307.1
LV164: JP821.4, Q329.1, Q330.1, R1313.1, R1315.1
LV165: JP826.4, Q331.1, Q332.1, R1321.1, R1323.1
LV166: JP831.4, Q333.1, Q334.1, R1329.1, R1331.1
LV167: JP836.4, Q335.1, Q336.1, R1337.1, R1339.1
RX2_HV: JP2.5, R8.2
RX2_HV1: JP7.5, R15.2
RX2_HV2: JP12.5, R23.2
RX2_HV3: JP17.5, R31.2
RX2_HV4: JP22.5, R39.2
RX2_HV5: JP27.5, R47.2
RX2_HV6: JP32.5, R55.2
RX2_HV7: JP37.5, R63.2
RX2_HV8: JP42.5, R71.2
RX2_HV9: JP47.5, R79.2
RX2_HV10: JP52.5, R87.2
RX2_HV11: JP57.5, R95.2
RX2_HV12: JP62.5, R103.2
RX2_HV13: JP67.5, R111.2
RX2_HV14: JP72.5, R119.2
RX2_HV15: JP77.5, R127.2
RX2_HV16: JP82.5, R135.2
RX2_HV17: JP87.5, R143.2
RX2_HV18: JP92.5, R151.2
RX2_HV19: JP97.5, R159.2
RX2_HV20: JP102.5, R167.2
RX2_HV21: JP107.5, R175.2
RX2_HV22: JP112.5, R183.2
RX2_HV23: JP117.5, R191.2
RX2_HV24: JP122.5, R199.2
RX2_HV25: JP127.5, R207.2
RX2_HV26: JP132.5, R215.2
RX2_HV27: JP137.5, R223.2
RX2_HV28: JP142.5, R231.2
RX2_HV29: JP147.5, R239.2
RX2_HV30: JP152.5, R247.2
RX2_HV31: JP157.5, R255.2
RX2_HV32: JP162.5, R263.2
RX2_HV33: JP167.5, R271.2
RX2_HV34: JP172.5, R279.2
RX2_HV35: JP177.5, R287.2
RX2_HV36: JP182.5, R295.2
RX2_HV37: JP187.5, R303.2
RX2_HV38: JP192.5, R311.2
RX2_HV39: JP197.5, R319.2
RX2_HV40: JP202.5, R327.2
RX2_HV41: JP207.5, R335.2
RX2_HV42: JP212.5, R343.2
RX2_HV43: JP217.5, R351.2
RX2_HV44: JP222.5, R359.2
RX2_HV45: JP227.5, R367.2
RX2_HV46: JP232.5, R375.2
RX2_HV47: JP237.5, R383.2
RX2_HV48: JP242.5, R391.2
RX2_HV49: JP247.5, R399.2
RX2_HV50: JP252.5, R407.2
RX2_HV51: JP257.5, R415.2
RX2_HV52: JP262.5, R423.2
RX2_HV53: JP267.5, R431.2
RX2_HV54: JP272.5, R439.2
RX2_HV55: JP277.5, R447.2
RX2_HV56: JP282.5, R455.2
RX2_HV57: JP287.5, R463.2
RX2_HV58: JP292.5, R471.2
RX2_HV59: JP297.5, R479.2
RX2_HV60: JP302.5, R487.2
RX2_HV61: JP307.5, R495.2
RX2_HV62: JP312.5, R503.2
RX2_HV63: JP317.5, R511.2
RX2_HV64: JP322.5, R519.2
RX2_HV65: JP327.5, R527.2
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
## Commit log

2013-06-13 Adding Board and Schematic Eagle Files v13
    Changed all resistor packages from 0402 to 0603. Nudged resistors,
    which caused minor trace re-routing. Also changed text font to Vector.
    Updated Sparkfun Logo and added the Open Hardware logo.
2013-06-13 Schematic Cleanup and Gitignore
    Changed net labels to updated SFE standards.
2013-06-24 Resistor Value Changes and Revision Code Update
    Changed the vales of r5 and r9 resistors from 10k to 20k. Added the
    revision # to the schematic.
2013-06-26 Updated Voltage Table / Added Creative Commons/Rev
    Changed the Example Voltage table to reflect the new resistor values as
    well as added an equation for reference. Added the creative commons
    license and designed by/revised by names.
2013-07-18 Created Panels
    Created Giant panel for MYDATA and smaller panels for manncorp
2013-07-18 smaller panel
    here is the smaller panel
2013-09-20 Small typo updates to schematic.
